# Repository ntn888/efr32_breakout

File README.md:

# efr32 Module Breakout

Mini breakout for ZYZBP008 Modoule housing an `EFR32MG21A020F768IM32`. See `efr32-module-breakout` dir for current. The other dir is an early version with `Tuya ZS3L`.

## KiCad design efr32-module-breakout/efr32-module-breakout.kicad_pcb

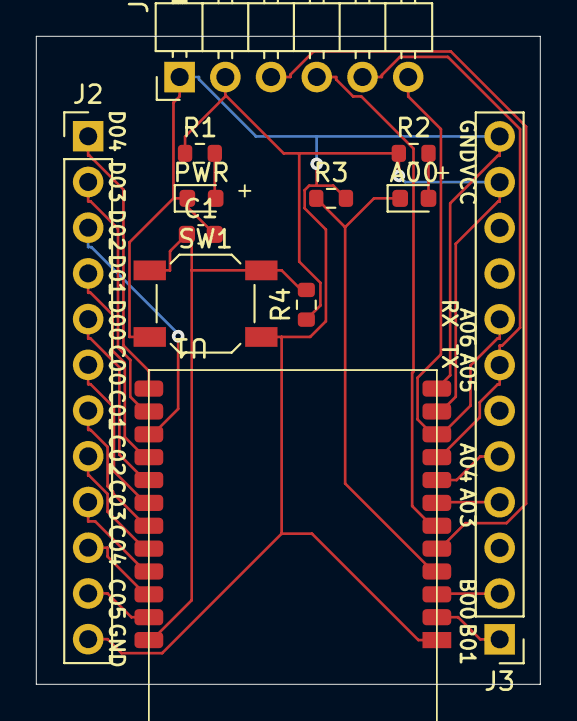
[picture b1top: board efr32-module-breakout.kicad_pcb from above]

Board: 2 copper layers, 28.0 x 36.0 mm, 12 parts (0 on the bottom side), 25 nets.

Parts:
A00: LED; LED_0603_1608Metric
C1: 0.1uF; C_0603_1608Metric
J1: Conn_01x06; PinHeader_1x06_P2.54mm_Horizontal
J2, J3: Conn_01x12; PinHeader_1x12_P2.54mm_Vertical
PWR: LED; LED_0603_1608Metric
R1, R3: 1K; R_0603_1608Metric
R2: 330; R_0603_1608Metric
R4: 10K; R_0603_1608Metric
SW1: SW_Push; SW_SPST_SKQG_WithoutStem
U1: ZYZBP008; ZYZBP008_module

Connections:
GND: C1.2, J1.1, J2.12, J3.12, PWR.1 (K), R3.2, SW1.2, U1.1 (GND), U1.12 (GND)
unnamed: PWR.2 (A), R1.2
unnamed: A00.2 (A), R2.2
PA03: J3.4, U1.7 (PA03)
PA04: J3.5, U1.8 (PA04)
PB00: J3.2, U1.3 (PB00)
PB01: J3.1, U1.2 (PB01)
PC00: J2.6, U1.18 (PC00)
PC01: J2.7, U1.19 (PC01)
PC02: J2.8, U1.20 (PC02)
PC03: J2.9, U1.21 (PC03)
PC04: J2.10, U1.22 (PC04)
PC05: J2.11, U1.23 (PC05)
PD00: J2.5, U1.17 (PD00)
PD01: J2.4, U1.16 (PD01)
PD02: J2.3, U1.15 (PD02)
PD03: J2.2, U1.14 (PD03)
PD04: J2.1, U1.13 (PD04)
RST: C1.1, R4.2, SW1.1, U1.24 (nRST)
VCC: J1.2, J3.11, R1.1, R2.1, R4.1, U1.11 (VCC)
rx: J1.6, J3.8, U1.10 (PA06/RXD)
swdclk: J1.3, U1.5 (PA01/SWCLK)
swdio: J1.4, U1.6 (PA02/SWDIO)
tx: J1.5, J3.7, U1.9 (PA05/TXD)
usr_led: A00.1 (K), R3.1, U1.4 (PA00)

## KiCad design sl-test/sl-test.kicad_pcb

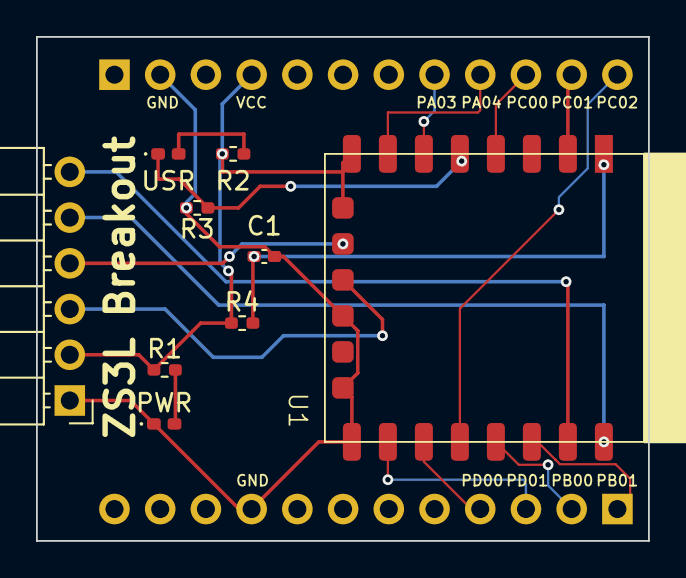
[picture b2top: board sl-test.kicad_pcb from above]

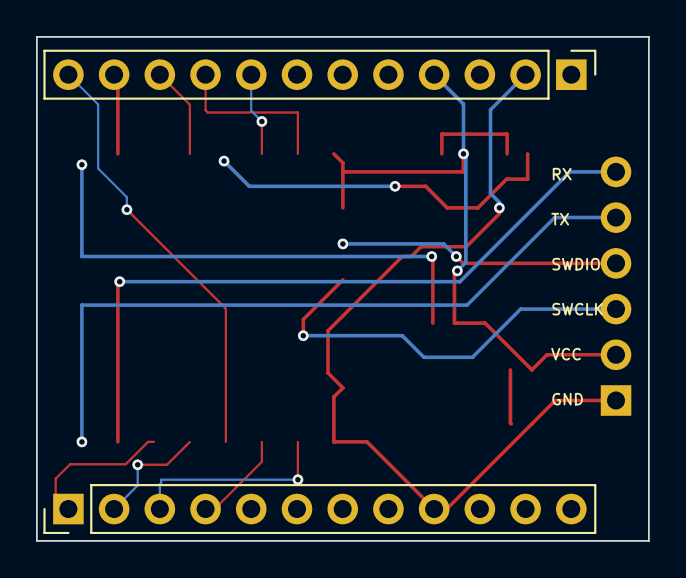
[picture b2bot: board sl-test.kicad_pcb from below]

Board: 4 copper layers, 34.0 x 28.0 mm, 11 parts (2 on the bottom side), 19 nets.

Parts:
C1: 0.1uF; C_0402_1005Metric_Pad0.74x0.62mm_HandSolder
J1: FTDI; PinHeader_1x06_P2.54mm_Horizontal
J6: IO1; PinHeader_1x12_P2.54mm_Vertical
J7: IO2; PinHeader_1x12_P2.54mm_Vertical
PWR: LED; LED_0402_1005Metric_Pad0.77x0.64mm_HandSolder
R1, R3: 1K; R_0402_1005Metric_Pad0.72x0.64mm_HandSolder
R2: 330; R_0402_1005Metric_Pad0.72x0.64mm_HandSolder
R4: 10k; R_0402_1005Metric_Pad0.72x0.64mm_HandSolder
U1: ZS3L
USR: LED; LED_0402_1005Metric_Pad0.77x0.64mm_HandSolder

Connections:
GND: C1.2, J1.1, J6.2, J7.9, PWR.1 (K), R3.2, U1.9 (GND), U1.20 (GND1), U1.22 (GND2)
unnamed: PWR.2 (A), R1.2
unnamed: R2.2, USR.2 (A)
PA03: J6.8, U1.6 (PA03)
PA04: J6.9, U1.7 (PA04)
PB00: J7.2, U1.13 (PB00)
PB01: J7.1, U1.14 (PB01)
PC00: J6.10, U1.4 (PC00)
PC01: J6.11, U1.2 (ADC_PC01)
PC02: J6.12, U1.12 (PC02)
PD00: J7.4, U1.11 (PD00)
PD01: J7.3, U1.10 (PD01)
RST: C1.1, R4.2, U1.1 (RST)
VCC: J1.2, J6.4, R1.1, R2.1, R4.1, U1.8 (VCC), U1.17 (3V3)
rx: J1.6, U1.15 (RXD)
swclk: J1.3, U1.19 (SWCLK)
swdio: J1.4, U1.18 (SWDIO)
tx: J1.5, U1.16 (TXD)
usr_led: R3.1, U1.5 (PA00), USR.1 (K)

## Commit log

2025-02-15 add version 0.2
2025-02-16 change button footprint
2025-02-16 adopt pcbway
